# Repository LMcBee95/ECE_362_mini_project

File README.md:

//---------Purdue University Spring 2016 ECE 362 Final Project---------//

Authors:
        Charles Li
        Swati Garg
        Ryan McBee
        Luke McBee

Project Title:
        DigiNerf Gun

Synopsis:
      These are the EAGLE files for my group's mini project for ECE 362.
      This PCB uses the micro controller used in the class, and 
      interfaces it with different peripherals. The board contains header 
      pins for the microcontroller, one shift register for an lcd 
      display, and two shift registers for leds.

      The major features of this gun include:
          x Multiple firing option usign pushbuttons to recieve input from the user
          x Variable firing speed by controller a power MOSFET using PWM
          x Battery monitoring using ATD
          x Piston arm reset incase of jamming
//---------------------------------------------------------------------//

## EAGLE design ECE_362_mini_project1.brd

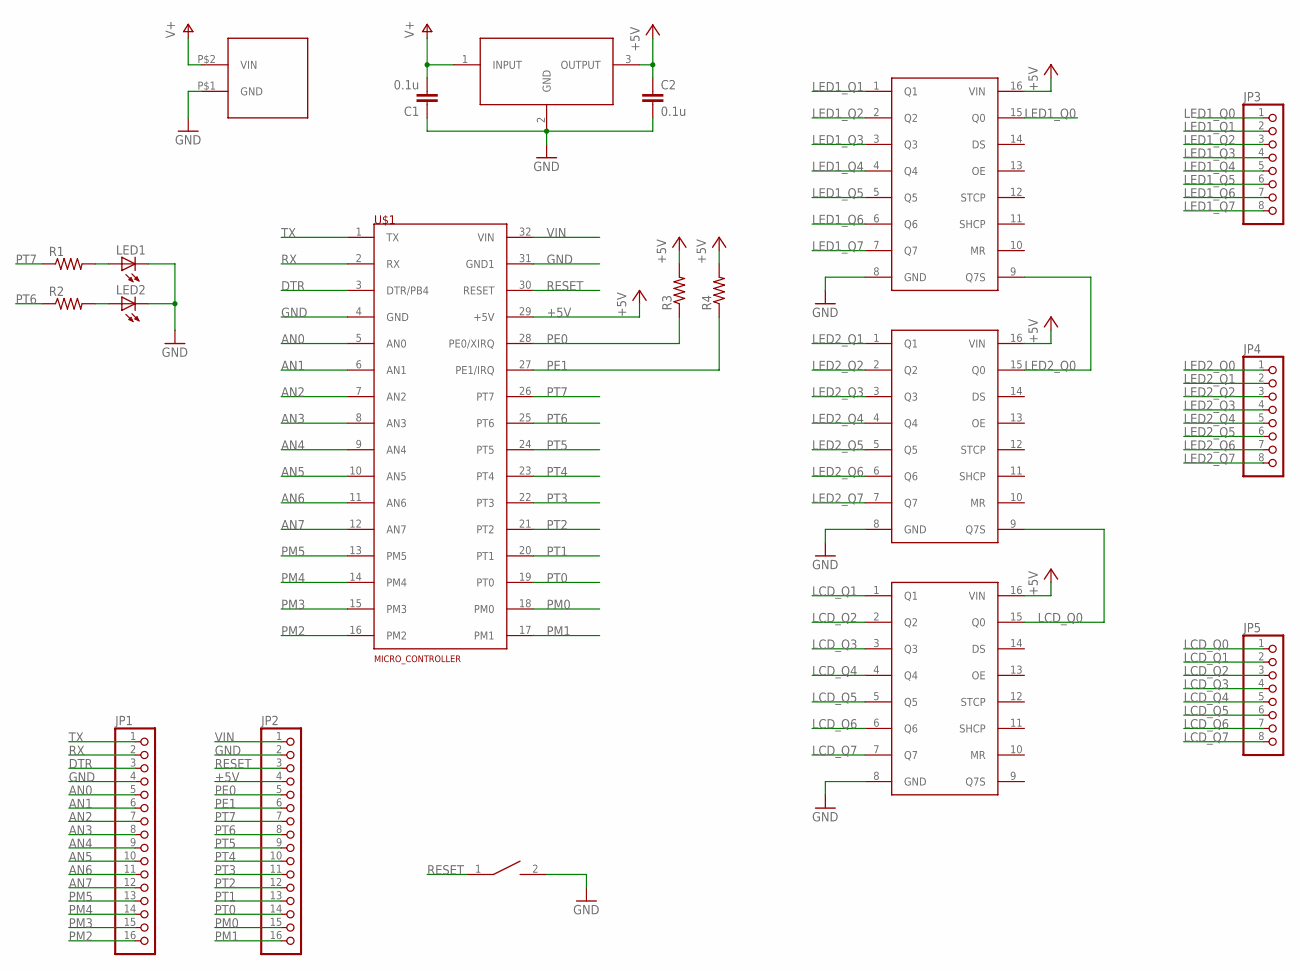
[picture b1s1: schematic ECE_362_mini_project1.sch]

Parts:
BOOT_SW: SWITCH; SW_2512
C1, C2: 0.1u; C0603
JP1, JP2: PINHD-1X16; 1X16
JP3, JP4, JP5: PINHD-1X8; 1X08
LED1, LED2: LEDCHIPLED_0603; CHIPLED_0603
R1, R2, R3, R4: R-US_R0603; R0603
U$1: MICRO_CONTROLLER
U$2, U$4, U$5: SHIFT_REGISTER; N5
U$3: XT60
U$6: L7805CV

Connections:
+5V: C2.1, JP2.4, R3.2, R4.2, U$1.29 (+5V), U$2.16 (VIN), U$4.16 (VIN), U$5.16 (VIN), U$6.3 (OUTPUT)
AN0: JP1.5, U$1.5 (AN0)
AN1: JP1.6, U$1.6 (AN1)
AN2: JP1.7, U$1.7 (AN2)
AN3: JP1.8, U$1.8 (AN3)
AN4: JP1.9, U$1.9 (AN4)
AN5: JP1.10, U$1.10 (AN5)
AN6: JP1.11, U$1.11 (AN6)
AN7: JP1.12, U$1.12 (AN7)
DTR: JP1.3, U$1.3 (DTR/PB4)
GND: BOOT_SW.2, C1.1, C2.2, JP1.4, JP2.2, LED1.C, LED2.C, U$1.4 (GND), U$1.31 (GND1), U$2.8 (GND), U$3.P$1 (GND), U$4.8 (GND), U$5.8 (GND), U$6.2 (GND)
LCD_Q0: JP5.1, U$4.9 (Q7S), U$5.15 (Q0)
LCD_Q1: JP5.2, U$5.1 (Q1)
LCD_Q2: JP5.3, U$5.2 (Q2)
LCD_Q3: JP5.4, U$5.3 (Q3)
LCD_Q4: JP5.5, U$5.4 (Q4)
LCD_Q5: JP5.6, U$5.5 (Q5)
LCD_Q6: JP5.7, U$5.6 (Q6)
LCD_Q7: JP5.8, U$5.7 (Q7)
LED1_Q0: JP3.1, U$2.15 (Q0)
LED1_Q1: JP3.2, U$2.1 (Q1)
LED1_Q2: JP3.3, U$2.2 (Q2)
LED1_Q3: JP3.4, U$2.3 (Q3)
LED1_Q4: JP3.5, U$2.4 (Q4)
LED1_Q5: JP3.6, U$2.5 (Q5)
LED1_Q6: JP3.7, U$2.6 (Q6)
LED1_Q7: JP3.8, U$2.7 (Q7)
LED2_Q0: JP4.1, U$2.9 (Q7S), U$4.15 (Q0)
LED2_Q1: JP4.2, U$4.1 (Q1)
LED2_Q2: JP4.3, U$4.2 (Q2)
LED2_Q3: JP4.4, U$4.3 (Q3)
LED2_Q4: JP4.5, U$4.4 (Q4)
LED2_Q5: JP4.6, U$4.5 (Q5)
LED2_Q6: JP4.7, U$4.6 (Q6)
LED2_Q7: JP4.8, U$4.7 (Q7)
unnamed: LED1.A, R1.2
unnamed: LED2.A, R2.2
PE0: JP2.5, R3.1, U$1.28 (PE0/XIRQ)
PE1: JP2.6, R4.1, U$1.27 (PE1/IRQ)
PM0: JP2.15, U$1.18 (PM0)
PM1: JP2.16, U$1.17 (PM1)
PM2: JP1.16, U$1.16 (PM2)
PM3: JP1.15, U$1.15 (PM3)
PM4: JP1.14, U$1.14 (PM4)
PM5: JP1.13, U$1.13 (PM5)
PT0: JP2.14, U$1.19 (PT0)
PT1: JP2.13, U$1.20 (PT1)
PT2: JP2.12, U$1.21 (PT2)
PT3: JP2.11, U$1.22 (PT3)
PT4: JP2.10, U$1.23 (PT4)
PT5: JP2.9, U$1.24 (PT5)
PT6: JP2.8, R2.1, U$1.25 (PT6)
PT7: JP2.7, R1.1, U$1.26 (PT7)
RESET: BOOT_SW.1, JP2.3, U$1.30 (RESET)
RX: JP1.2, U$1.2 (RX)
TX: JP1.1, U$1.1 (TX)
V+: C1.2, U$3.P$2 (VIN), U$6.1 (INPUT)
VIN: JP2.1, U$1.32 (VIN)

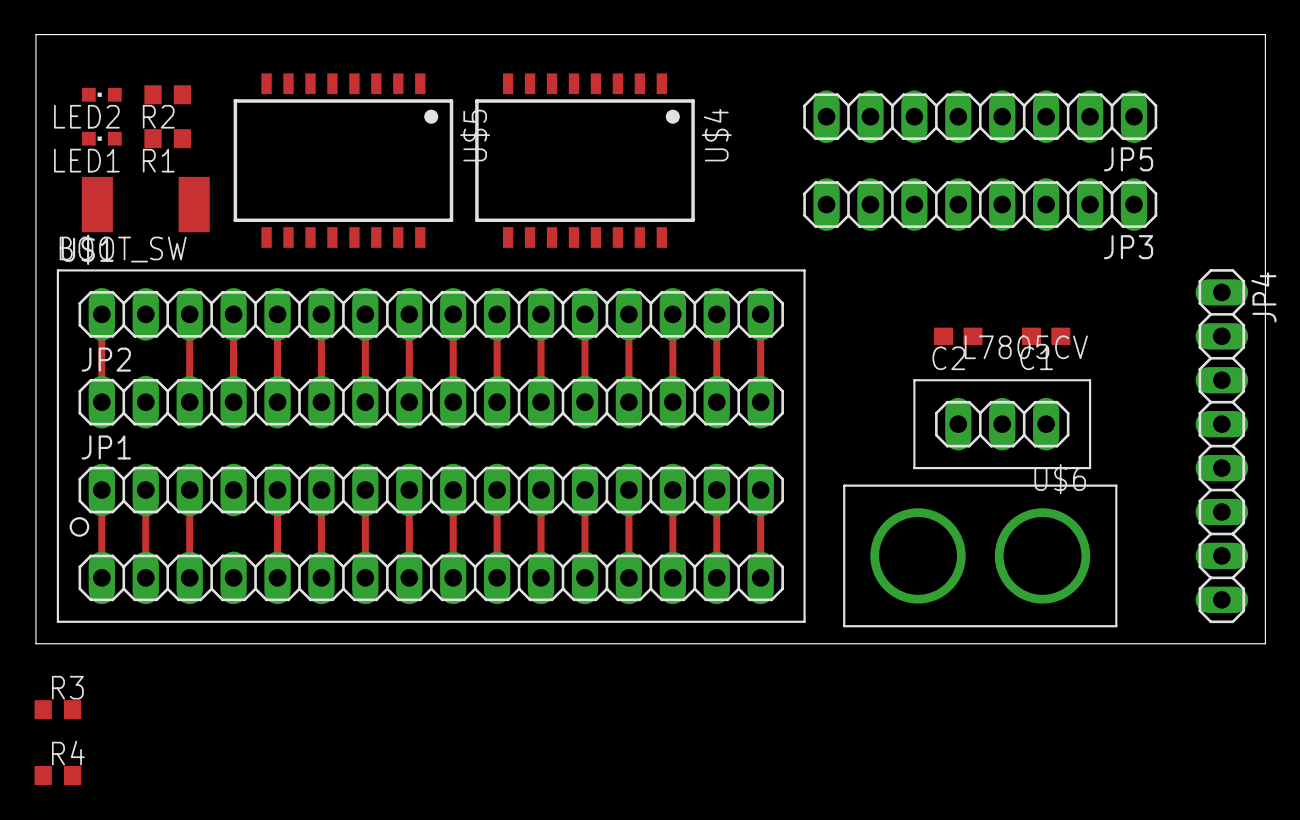
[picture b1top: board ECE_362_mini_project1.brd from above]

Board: 2 copper layers, 71.1 x 35.2 mm, 20 parts (1 on the bottom side), 58 nets.

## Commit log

2016-03-29 Updated the board
2016-03-30 rouding out some final errors
2016-03-30 cosmetic changes
